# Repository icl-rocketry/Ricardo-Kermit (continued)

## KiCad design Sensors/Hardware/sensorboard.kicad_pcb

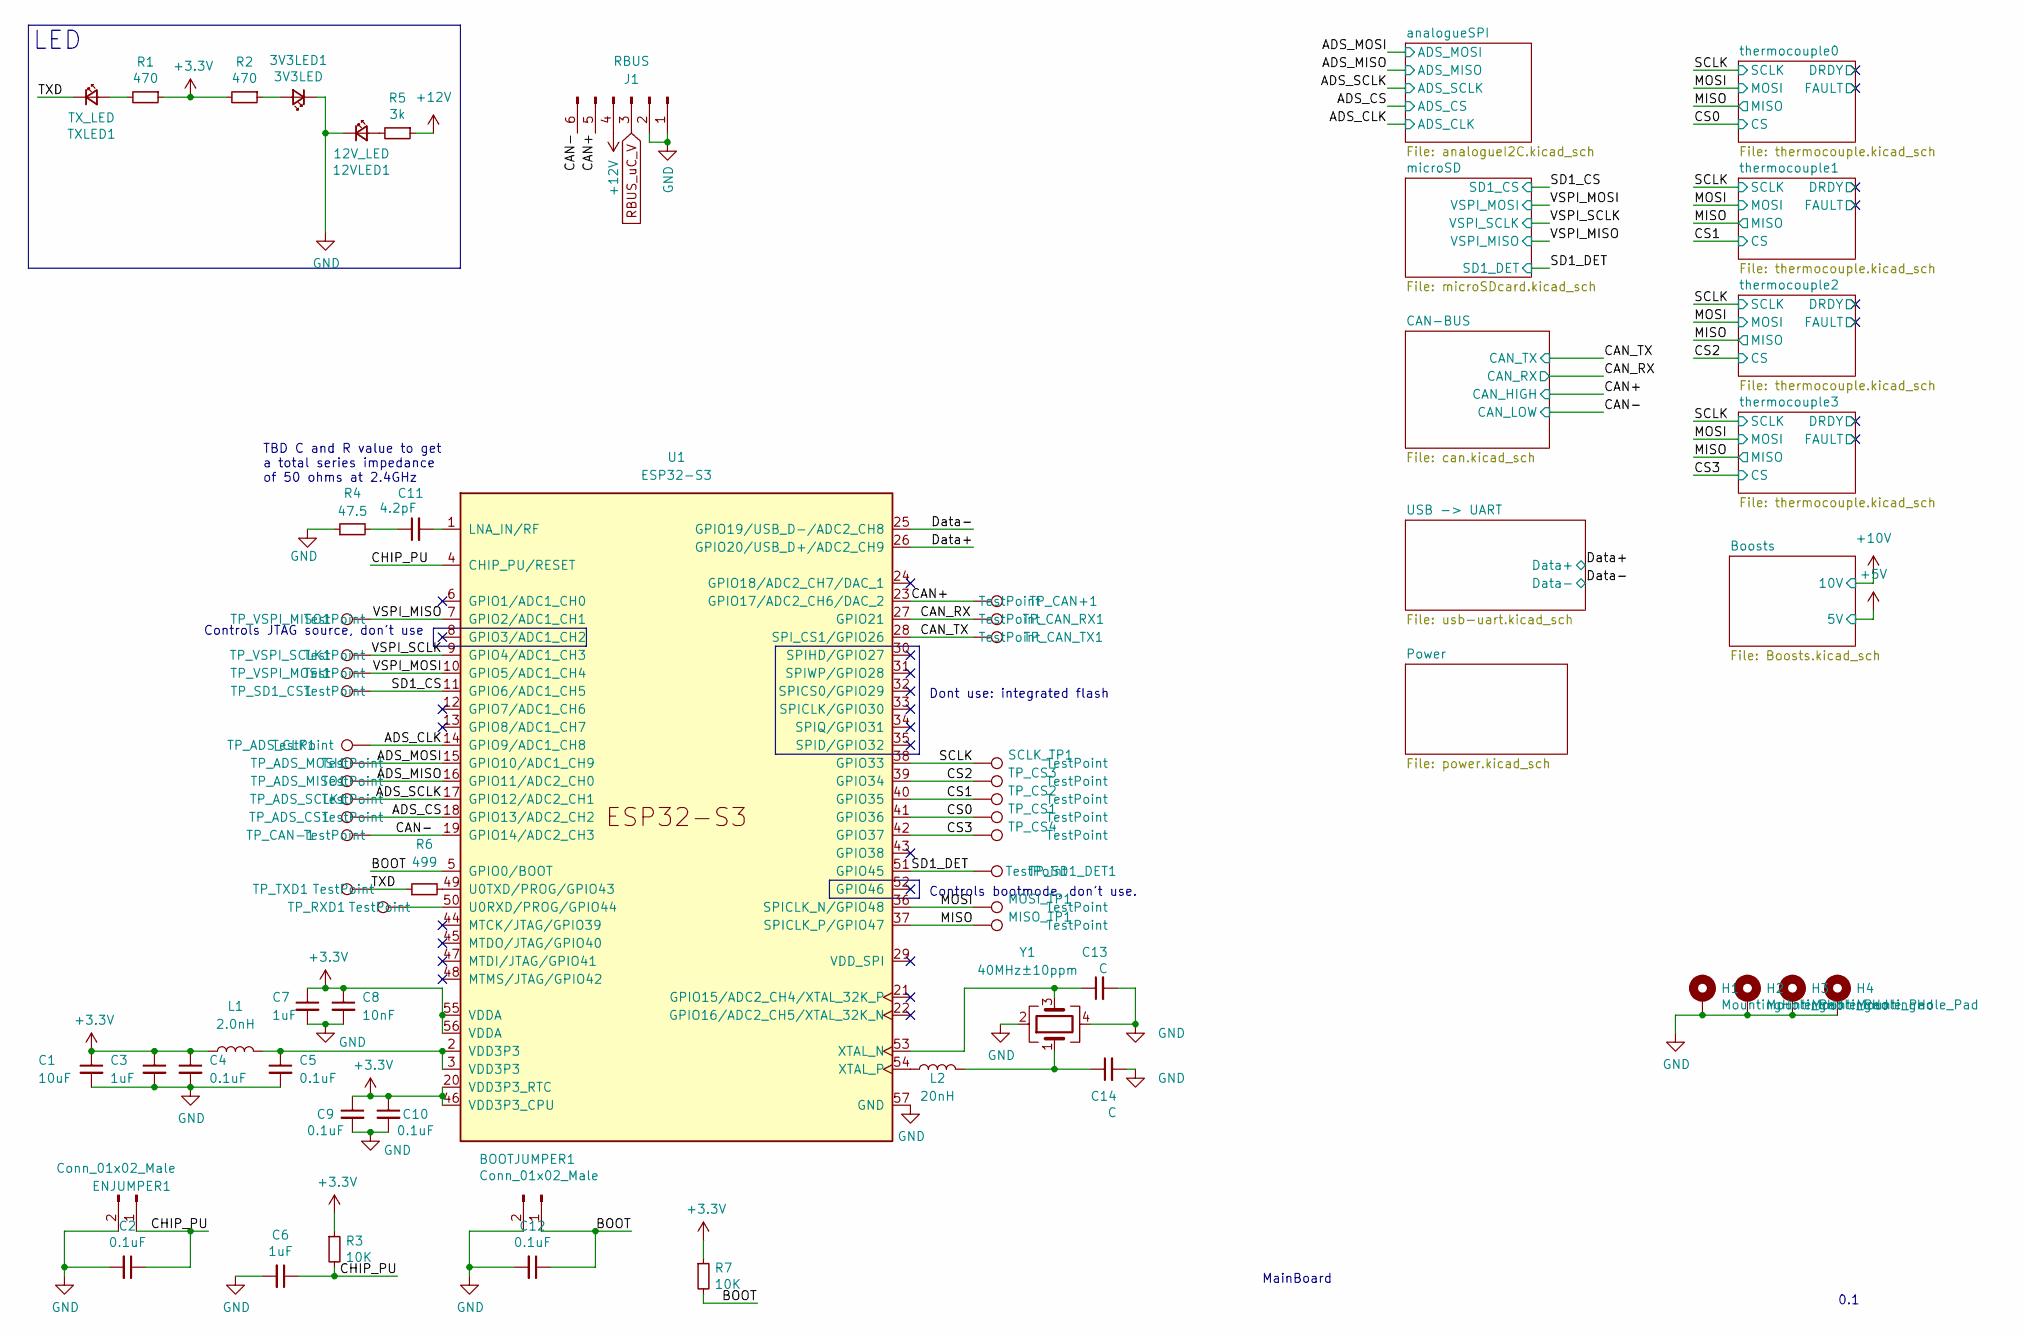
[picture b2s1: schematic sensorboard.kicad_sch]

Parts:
3V3LED1: 3V3LED; LED_0603_1608Metric
12VLED1: 12V_LED; LED_0603_1608Metric
BOOTJUMPER1: Conn_01x02_Male; PinHeader_1x02_P2.54mm_Vertical
C1: 10uF; C_0402_1005Metric
C2, C4, C5, C9, C10, C12: 0.1uF; C_0402_1005Metric
C3, C6, C7: 1uF; C_0402_1005Metric
C8: 10nF; C_0402_1005Metric
C11: 4.2pF; C_0402_1005Metric
C13, C14: C; C_0603_1608Metric
ENJUMPER1: Conn_01x02_Male; PinHeader_1x02_P2.54mm_Vertical
H1, H2, H3, H4: MountingHole_Pad; MountingHole_3.2mm_M3_DIN965_Pad
J1: RBUS; Molex_Mini-Fit_Jr_5566-06A_2x03_P4.20mm_Vertical
L1: 2.0nH; L_0402_1005Metric
L2: 20nH; L_0402_1005Metric
MISO_TP1: TestPoint; TestPoint_Pad_D1.0mm
MOSI_TP1: TestPoint; TestPoint_Pad_D1.0mm
R1, R2: 470; R_0603_1608Metric
R3, R7: 10K; R_0402_1005Metric
R4: 47.5; R_0402_1005Metric
R5: 3k; R_0402_1005Metric
R6: 499; R_0402_1005Metric
SCLK_TP1: TestPoint; TestPoint_Pad_D1.0mm
TP_ADS_CLK1: TestPoint; TestPoint_Pad_D1.0mm
TP_ADS_CS1: TestPoint; TestPoint_Pad_D1.0mm
TP_ADS_MISO1: TestPoint; TestPoint_Pad_D1.0mm
TP_ADS_MOSI1: TestPoint; TestPoint_Pad_D1.0mm
TP_ADS_SCLK1: TestPoint; TestPoint_Pad_D1.0mm
TP_CAN+1: TestPoint; TestPoint_Pad_D1.0mm
TP_CAN-1: TestPoint; TestPoint_Pad_D1.0mm
TP_CAN_RX1: TestPoint; TestPoint_Pad_D1.0mm
TP_CAN_TX1: TestPoint; TestPoint_Pad_D1.0mm
TP_CS1, TP_CS2, TP_CS3, TP_CS4: TestPoint; TestPoint_Pad_D1.0mm
TP_RXD1: TestPoint; TestPoint_Pad_D1.0mm
TP_SD1_CS1, TP_SD1_DET1: TestPoint; TestPoint_Pad_D1.0mm
TP_TXD1: TestPoint; TestPoint_Pad_D1.0mm
TP_VSPI_MISO1: TestPoint; TestPoint_Pad_D1.0mm
TP_VSPI_MOSI1: TestPoint; TestPoint_Pad_D1.0mm
TP_VSPI_SCLK1: TestPoint; TestPoint_Pad_D1.0mm
TXLED1: TX_LED; LED_0603_1608Metric
U1: ESP32-S3; QFN-56-1EP_7x7mm_P0.4mm_EP5.6x5.6mm
Y1: 40MHz±10ppm; Crystal_SMD_2016-4Pin_2.0x1.6mm

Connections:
+3V3: C1.1, C3.1, C4.1, C7.1, C8.1, C9.1, C10.1, L1.1, R1.1, R2.2, R3.1, R7.1, U1.20 (VDD3P3_RTC), U1.46 (VDD3P3_CPU), U1.55 (VDDA), U1.56 (VDDA); also elsewhere on the board
+12V: J1.4, R5.1
/ADS_CLK: TP_ADS_CLK1.1, U1.14 (GPIO9/ADC1_CH8); also elsewhere on the board
/ADS_CS: TP_ADS_CS1.1, U1.18 (GPIO13/ADC2_CH2); also elsewhere on the board
/ADS_MISO: TP_ADS_MISO1.1, U1.16 (GPIO11/ADC2_CH0); also elsewhere on the board
/ADS_MOSI: TP_ADS_MOSI1.1, U1.15 (GPIO10/ADC1_CH9); also elsewhere on the board
/ADS_SCLK: TP_ADS_SCLK1.1, U1.17 (GPIO12/ADC2_CH1); also elsewhere on the board
/BOOT: BOOTJUMPER1.1, C12.1, R7.2, U1.5 (GPIO0/BOOT)
/CAN+: J1.5, TP_CAN+1.1, U1.23 (GPIO17/ADC2_CH6/DAC_2); also elsewhere on the board
/CAN-: J1.6, TP_CAN-1.1, U1.19 (GPIO14/ADC2_CH3); also elsewhere on the board
/CAN_RX: TP_CAN_RX1.1, U1.27 (GPIO21); also elsewhere on the board
/CAN_TX: TP_CAN_TX1.1, U1.28 (SPI_CS1/GPIO26); also elsewhere on the board
/CHIP_PU: C2.1, C6.1, ENJUMPER1.1, R3.2, U1.4 (CHIP_PU/RESET)
/CS0: TP_CS1.1, U1.41 (GPIO36); also elsewhere on the board
/CS1: TP_CS2.1, U1.40 (GPIO35); also elsewhere on the board
/CS2: TP_CS3.1, U1.39 (GPIO34); also elsewhere on the board
/CS3: TP_CS4.1, U1.42 (GPIO37); also elsewhere on the board
/Data+: U1.26 (GPIO20/USB_D+/ADC2_CH9); also elsewhere on the board
/Data-: U1.25 (GPIO19/USB_D-/ADC2_CH8); also elsewhere on the board
/MISO: MISO_TP1.1, U1.37 (SPICLK_P/GPIO47); also elsewhere on the board
/MOSI: MOSI_TP1.1, U1.36 (SPICLK_N/GPIO48); also elsewhere on the board
/SCLK: SCLK_TP1.1, U1.38 (GPIO33); also elsewhere on the board
/SD1_CS: TP_SD1_CS1.1, U1.11 (GPIO6/ADC1_CH5); also elsewhere on the board
/SD1_DET: TP_SD1_DET1.1, U1.51 (GPIO45); also elsewhere on the board
/TXD: R6.1, TP_TXD1.1, TXLED1.1 (K)
/VSPI_MISO: TP_VSPI_MISO1.1, U1.7 (GPIO2/ADC1_CH1); also elsewhere on the board
/VSPI_MOSI: TP_VSPI_MOSI1.1, U1.10 (GPIO5/ADC1_CH4); also elsewhere on the board
/VSPI_SCLK: TP_VSPI_SCLK1.1, U1.9 (GPIO4/ADC1_CH3); also elsewhere on the board
GND: 3V3LED1.1 (K), 12VLED1.1 (K), BOOTJUMPER1.2, C1.2, C2.2, C3.2, C4.2, C5.2, C6.2, C7.2, C8.2, C9.2, C10.2, C12.2, C13.2, C14.2, ENJUMPER1.2, H1.1, H2.1, H3.1, H4.1, J1.1, J1.2, R4.1, U1.57 (GND), Y1.2, Y1.4; also elsewhere on the board
unnamed: 3V3LED1.2 (A), R2.1
unnamed: 12VLED1.2 (A), R5.2
unnamed: C5.1, L1.2, U1.2 (VDD3P3), U1.3 (VDD3P3)
unnamed: C11.1, R4.2
unnamed: C14.1, L2.2, Y1.1
unnamed: R1.2, TXLED1.2 (A)
unnamed: C11.2, U1.1 (LNA_IN/RF)
unnamed: TP_RXD1.1, U1.50 (U0RXD/PROG/GPIO44)
unnamed: R6.2, U1.49 (U0TXD/PROG/GPIO43)
unnamed: C13.1, U1.53 (XTAL_N), Y1.3
unnamed: L2.1, U1.54 (XTAL_P)
RBUS_uC_V: J1.3; also elsewhere on the board

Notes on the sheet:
LED
Dont use: integrated flash
TBD C and R value to get a total series impedance of 50 ohms at 2.4GHz
MainBoard
0.1
Controls JTAG source, don't use
Controls bootmode, don't use.

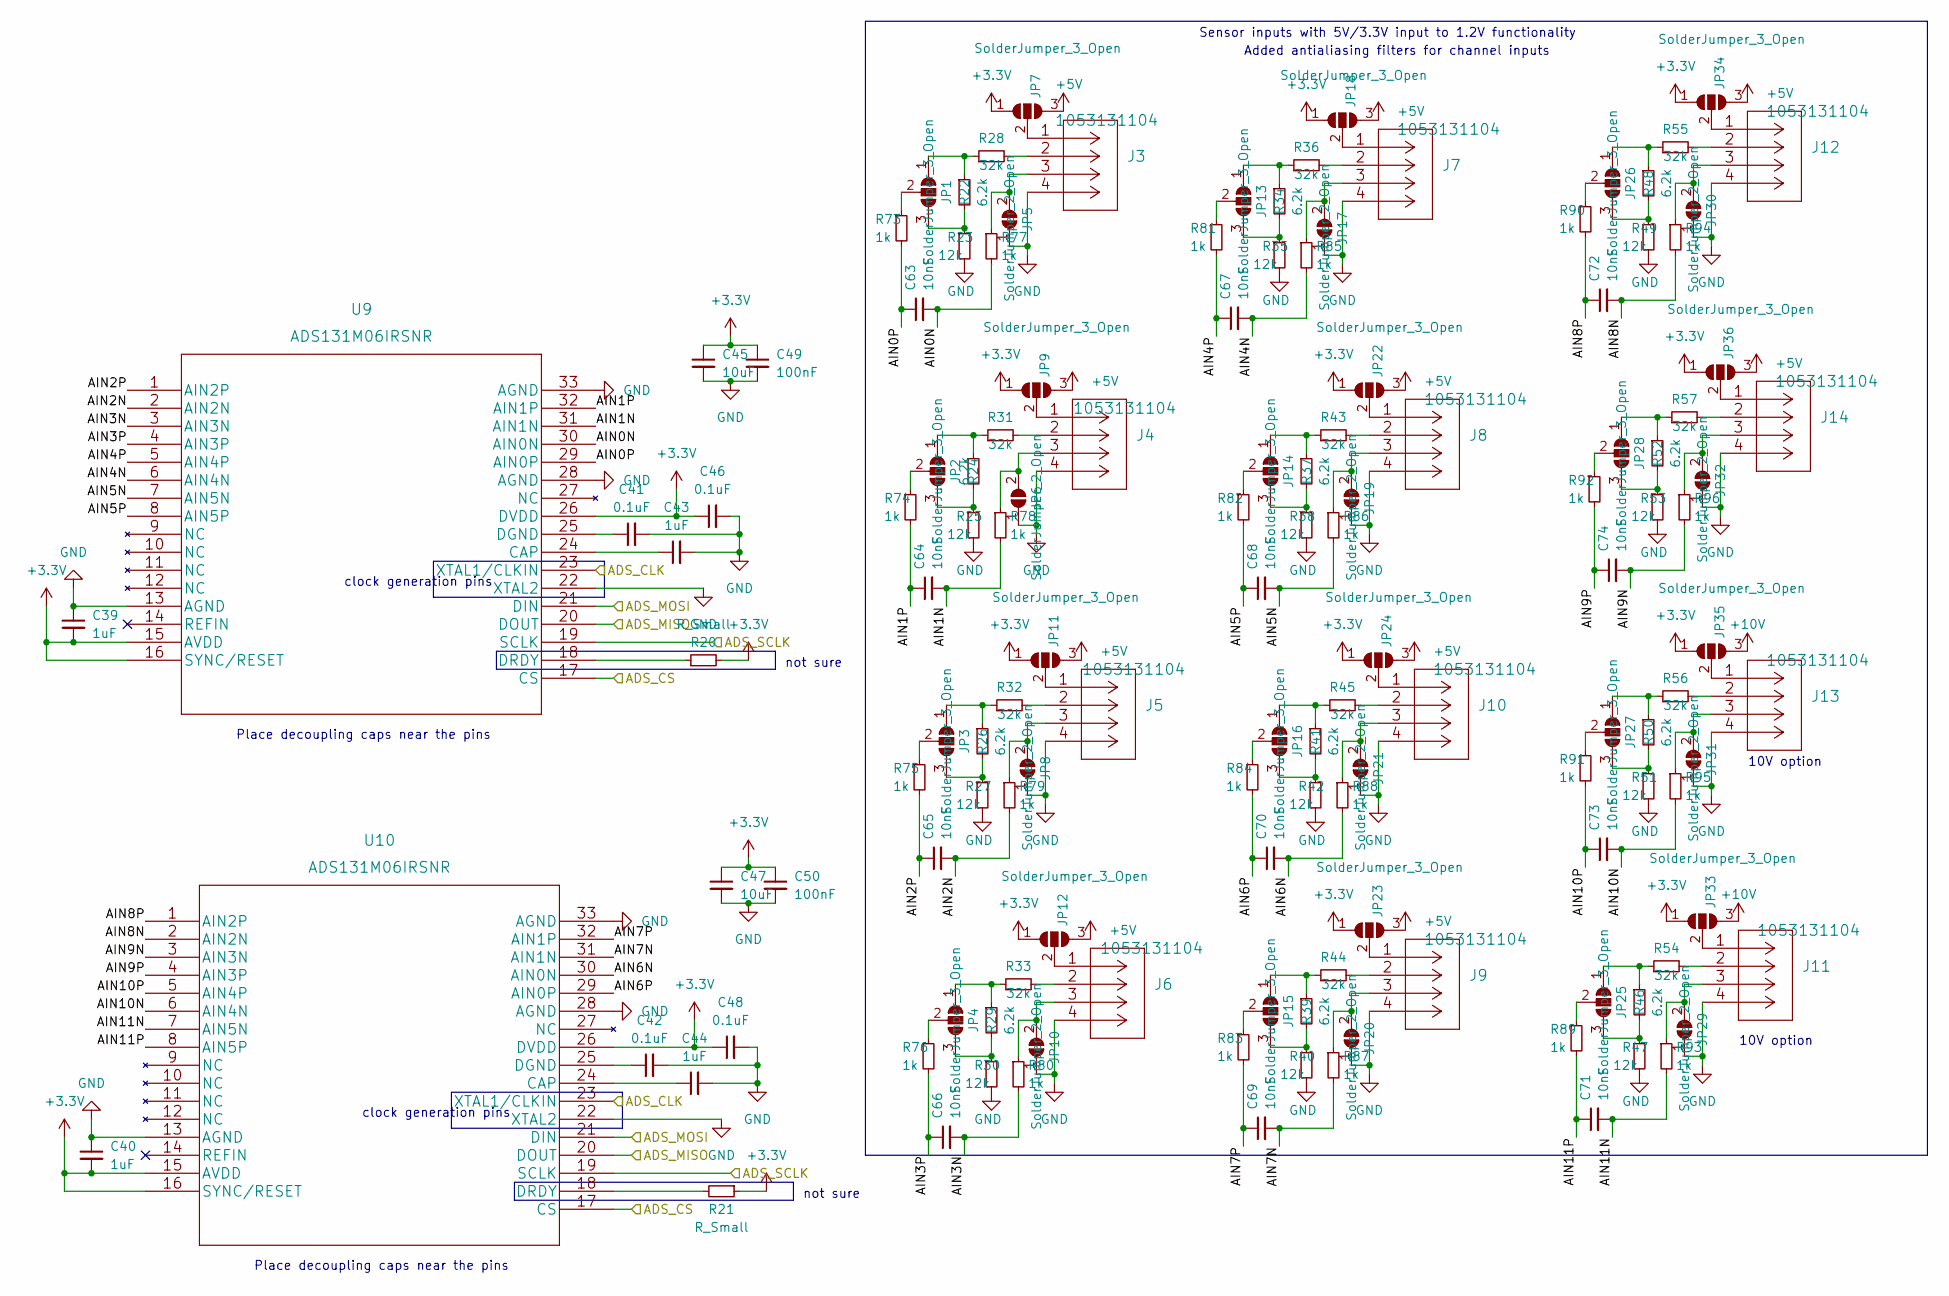
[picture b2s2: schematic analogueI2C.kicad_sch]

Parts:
C39, C40, C43, C44: 1uF; C_0402_1005Metric
C41, C42, C46, C48: 0.1uF; C_0402_1005Metric
C45, C47: 10uF; C_0402_1005Metric
C49, C50: 100nF; C_0402_1005Metric
C63, C64, C65, C66, C67, C68, C69, C70, C71, C72, C73, C74: 10nF; C_0402_1005Metric
J3, J4, J5, J6, J7, J8, J9, J10, J11, J12, J13, J14: 1053131104
JP1, JP2, JP3, JP4, JP7, JP9, JP11, JP12, JP13, JP14, JP15, JP16, JP18, JP22, JP23, JP24, JP25, JP26, JP27, JP28, JP33, JP34, JP35, JP36: SolderJumper_3_Open; SolderJumper-3_P1.3mm_Open_RoundedPad1.0x1.5mm_NumberLabels
JP5, JP6, JP8, JP10, JP17, JP19, JP20, JP21, JP29, JP30, JP31, JP32: SolderJumper_2_Open; SolderJumper-2_P1.3mm_Open_RoundedPad1.0x1.5mm
R20, R21: R_Small; R_0603_1608Metric
R22, R24, R26, R29, R34, R37, R39, R41, R46, R48, R50, R52: 6.2k; R_0402_1005Metric
R23, R25, R27, R30, R35, R38, R40, R42, R47, R49, R51, R53: 12k; R_0402_1005Metric
R28, R31, R32, R33, R36, R43, R44, R45, R54, R55, R56, R57: 32k; R_0402_1005Metric
R73, R74, R75, R76, R77, R78, R79, R80, R81, R82, R83, R84, R85, R86, R87, R88, R89, R90, R91, R92, R93, R94, R95, R96: 1k; R_0402_1005Metric
U9, U10: ADS131M06IRSNR

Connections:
+3V3: C39.2, C40.2, C45.1, C46.1, C47.1, C48.1, C49.1, C50.1, JP7.1 (A), JP9.1 (A), JP11.1 (A), JP12.1 (A), JP18.1 (A), JP22.1 (A), JP23.1 (A), JP24.1 (A), JP33.1 (A), JP34.1 (A), JP35.1 (A), JP36.1 (A), R20.2, R21.1, U9.15 (AVDD), U9.16 (SYNC/RESET), U9.26 (DVDD), U10.15 (AVDD), U10.16 (SYNC/RESET), U10.26 (DVDD); also elsewhere on the board
+5V: JP7.3 (B), JP9.3 (B), JP11.3 (B), JP12.3 (B), JP18.3 (B), JP22.3 (B), JP23.3 (B), JP24.3 (B), JP34.3 (B), JP36.3 (B); also elsewhere on the board
+10V: JP33.3 (B), JP35.3 (B); also elsewhere on the board
/ADS_CLK: U9.23 (XTAL1/CLKIN), U10.23 (XTAL1/CLKIN); also elsewhere on the board
/ADS_CS: U9.17 (CS), U10.17 (CS); also elsewhere on the board
/ADS_MISO: U9.20 (DOUT), U10.20 (DOUT); also elsewhere on the board
/ADS_MOSI: U9.21 (DIN), U10.21 (DIN); also elsewhere on the board
/ADS_SCLK: U9.19 (SCLK), U10.19 (SCLK); also elsewhere on the board
/analogueSPI/AIN0N: C63.2, R77.2, U9.30 (AIN0N)
/analogueSPI/AIN0P: C63.1, R73.2, U9.29 (AIN0P)
/analogueSPI/AIN1N: C64.2, R78.2, U9.31 (AIN1N)
/analogueSPI/AIN1P: C64.1, R74.2, U9.32 (AIN1P)
/analogueSPI/AIN2N: C65.2, R79.2, U9.2 (AIN2N)
/analogueSPI/AIN2P: C65.1, R75.2, U9.1 (AIN2P)
/analogueSPI/AIN3N: C66.2, R80.2, U9.3 (AIN3N)
/analogueSPI/AIN3P: C66.1, R76.2, U9.4 (AIN3P)
/analogueSPI/AIN4N: C67.2, R85.2, U9.6 (AIN4N)
/analogueSPI/AIN4P: C67.1, R81.2, U9.5 (AIN4P)
/analogueSPI/AIN5N: C68.2, R86.2, U9.7 (AIN5N)
/analogueSPI/AIN5P: C68.1, R82.2, U9.8 (AIN5P)
/analogueSPI/AIN6N: C70.2, R88.2, U10.30 (AIN0N)
/analogueSPI/AIN6P: C70.1, R84.2, U10.29 (AIN0P)
/analogueSPI/AIN7N: C69.2, R87.2, U10.31 (AIN1N)
/analogueSPI/AIN7P: C69.1, R83.2, U10.32 (AIN1P)
/analogueSPI/AIN8N: C72.2, R94.2, U10.2 (AIN2N)
/analogueSPI/AIN8P: C72.1, R90.2, U10.1 (AIN2P)
/analogueSPI/AIN9N: C74.2, R96.2, U10.3 (AIN3N)
/analogueSPI/AIN9P: C74.1, R92.2, U10.4 (AIN3P)
/analogueSPI/AIN10N: C73.2, R95.2, U10.6 (AIN4N)
/analogueSPI/AIN10P: C73.1, R91.2, U10.5 (AIN4P)
/analogueSPI/AIN11N: C71.2, R93.2, U10.7 (AIN5N)
/analogueSPI/AIN11P: C71.1, R89.2, U10.8 (AIN5P)
GND: C39.1, C40.1, C41.2, C42.2, C43.2, C44.2, C45.2, C46.2, C47.2, C48.2, C49.2, C50.2, J3.4, J4.4, J5.4, J6.4, J7.4, J8.4, J9.4, J10.4, J11.4, J12.4, J13.4, J14.4, JP5.1 (A), JP6.1 (A), JP8.1 (A), JP10.1 (A), JP17.1 (A), JP19.1 (A), JP20.1 (A), JP21.1 (A), JP29.1 (A), JP30.1 (A), JP31.1 (A), JP32.1 (A), R23.2, R25.2, R27.2, R30.2, R35.2, R38.2, R40.2, R42.2, R47.2, R49.2, R51.2, R53.2, U9.13 (AGND), U9.22 (XTAL2), U9.28 (AGND), U9.33 (AGND), U10.13 (AGND), U10.22 (XTAL2), U10.28 (AGND), U10.33 (AGND); also elsewhere on the board
unnamed: J3.2, R28.2
unnamed: J4.2, R31.2
unnamed: J5.2, R32.2
unnamed: J6.2, R33.2
unnamed: J7.2, R36.2
unnamed: J8.2, R43.2
unnamed: J9.2, R44.2
unnamed: J10.2, R45.2
unnamed: J11.2, R54.2
unnamed: J12.2, R55.2
unnamed: J13.2, R56.2
unnamed: J14.2, R57.2
unnamed: JP1.1 (A), R22.1, R28.1
unnamed: JP1.3 (B), R22.2, R23.1
unnamed: JP1.2 (C), R73.1
unnamed: JP2.1 (A), R24.1, R31.1
unnamed: JP2.3 (B), R24.2, R25.1
unnamed: JP2.2 (C), R74.1
unnamed: JP3.1 (A), R26.1, R32.1
unnamed: JP3.3 (B), R26.2, R27.1
unnamed: JP3.2 (C), R75.1
unnamed: JP4.1 (A), R29.1, R33.1
unnamed: JP4.3 (B), R29.2, R30.1
unnamed: JP4.2 (C), R76.1
unnamed: J3.3, JP5.2 (B), R77.1
unnamed: J4.3, JP6.2 (B), R78.1
unnamed: J3.1, JP7.2 (C)
unnamed: J5.3, JP8.2 (B), R79.1
unnamed: J4.1, JP9.2 (C)
unnamed: J6.3, JP10.2 (B), R80.1
unnamed: J5.1, JP11.2 (C)
unnamed: J6.1, JP12.2 (C)
unnamed: JP13.1 (A), R34.1, R36.1
unnamed: JP13.3 (B), R34.2, R35.1
unnamed: JP13.2 (C), R81.1
unnamed: JP14.1 (A), R37.1, R43.1
unnamed: JP14.3 (B), R37.2, R38.1
unnamed: JP14.2 (C), R82.1
unnamed: JP15.1 (A), R39.1, R44.1
unnamed: JP15.3 (B), R39.2, R40.1
unnamed: JP15.2 (C), R83.1
unnamed: JP16.1 (A), R41.1, R45.1
unnamed: JP16.3 (B), R41.2, R42.1
unnamed: JP16.2 (C), R84.1
unnamed: J7.3, JP17.2 (B), R85.1
unnamed: J7.1, JP18.2 (C)
unnamed: J8.3, JP19.2 (B), R86.1
unnamed: J9.3, JP20.2 (B), R87.1
unnamed: J10.3, JP21.2 (B), R88.1
unnamed: J8.1, JP22.2 (C)
unnamed: J9.1, JP23.2 (C)
unnamed: J10.1, JP24.2 (C)
unnamed: JP25.1 (A), R46.1, R54.1
unnamed: JP25.3 (B), R46.2, R47.1
unnamed: JP25.2 (C), R89.1
unnamed: JP26.1 (A), R48.1, R55.1
unnamed: JP26.3 (B), R48.2, R49.1
unnamed: JP26.2 (C), R90.1
unnamed: JP27.1 (A), R50.1, R56.1
unnamed: JP27.3 (B), R50.2, R51.1
unnamed: JP27.2 (C), R91.1
unnamed: JP28.1 (A), R52.1, R57.1
unnamed: JP28.3 (B), R52.2, R53.1
unnamed: JP28.2 (C), R92.1
unnamed: J11.3, JP29.2 (B), R93.1
unnamed: J12.3, JP30.2 (B), R94.1
unnamed: J13.3, JP31.2 (B), R95.1
unnamed: J14.3, JP32.2 (B), R96.1
unnamed: J11.1, JP33.2 (C)
unnamed: J12.1, JP34.2 (C)
unnamed: J13.1, JP35.2 (C)
unnamed: J14.1, JP36.2 (C)
unnamed: C43.1, U9.24 (CAP)
unnamed: C41.1, U9.25 (DGND)
unnamed: R20.1, U9.18 (DRDY)
unnamed: C44.1, U10.24 (CAP)
unnamed: C42.1, U10.25 (DGND)
unnamed: R21.2, U10.18 (DRDY)

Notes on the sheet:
Added antialiasing filters for channel inputs
10V option
clock generation pins
not sure
Sensor inputs with 5V/3.3V input to 1.2V functionality
Place decoupling caps near the pins

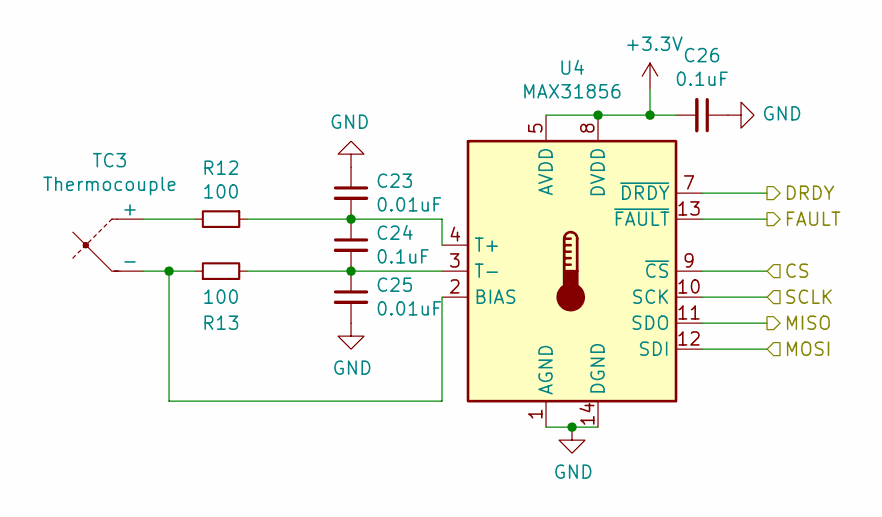
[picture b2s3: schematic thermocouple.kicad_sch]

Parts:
C23, C25: 0.01uF; C_0402_1005Metric
C24, C26: 0.1uF; C_0402_1005Metric
R12, R13: 100; R_0402_1005Metric
TC3: Thermocouple; TerminalBlock_TE_282834-2_1x02_P2.54mm_Horizontal
U4: MAX31856; TSSOP-14_4.4x5mm_P0.65mm

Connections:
+3V3: C26.2, U4.5 (AVDD), U4.8 (DVDD); also elsewhere on the board
/CS3: U4.9 (~CS); also elsewhere on the board
/MISO: U4.11 (SDO); also elsewhere on the board
/MOSI: U4.12 (SDI); also elsewhere on the board
/SCLK: U4.10 (SCK); also elsewhere on the board
/thermocouple3/DRDY: U4.7 (~DRDY)
/thermocouple3/FAULT: U4.13 (~FAULT)
GND: C23.1, C25.2, C26.1, U4.1 (AGND), U4.14 (DGND); also elsewhere on the board
unnamed: R12.2, TC3.1 (+)
unnamed: R13.1, TC3.2 (-), U4.2 (BIAS)
unnamed: C23.2, C24.1, R12.1, U4.4 (T+)
unnamed: C24.2, C25.1, R13.2, U4.3 (T-)

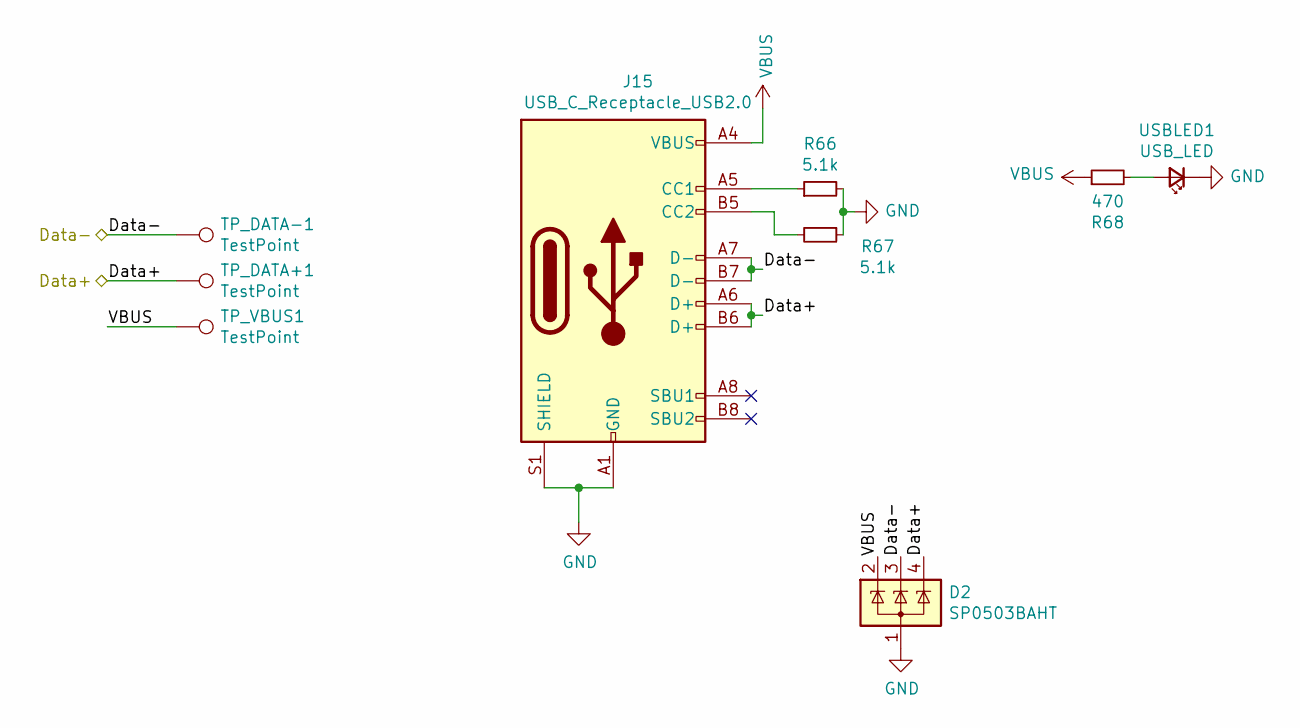
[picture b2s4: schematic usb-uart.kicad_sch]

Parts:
D2: SP0503BAHT; SOT-143
J15: USB_C_Receptacle_USB2.0; USB_C_Receptacle_Palconn_UTC16-G
R66, R67: 5.1k; R_0402_1005Metric
R68: 470; R_0402_1005Metric
TP_DATA+1: TestPoint; TestPoint_Pad_D1.0mm
TP_DATA-1: TestPoint; TestPoint_Pad_D1.0mm
TP_VBUS1: TestPoint; TestPoint_Pad_D1.0mm
USBLED1: USB_LED; LED_0603_1608Metric

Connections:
/Data+: D2.4 (K), J15.A6 (D+), J15.B6 (D+), TP_DATA+1.1; also elsewhere on the board
/Data-: D2.3 (K), J15.A7 (D-), J15.B7 (D-), TP_DATA-1.1; also elsewhere on the board
GND: D2.1 (A), J15.A1 (GND), J15.A12 (GND), J15.B1 (GND), J15.B12 (GND), J15.S1 (SHIELD), R66.2, R67.1, USBLED1.1 (K); also elsewhere on the board
unnamed: J15.A5 (CC1), R66.1
unnamed: J15.B5 (CC2), R67.2
unnamed: R68.2, USBLED1.2 (A)
VBUS: D2.2 (K), J15.A4 (VBUS), J15.A9 (VBUS), J15.B4 (VBUS), J15.B9 (VBUS), R68.1, TP_VBUS1.1; also elsewhere on the board

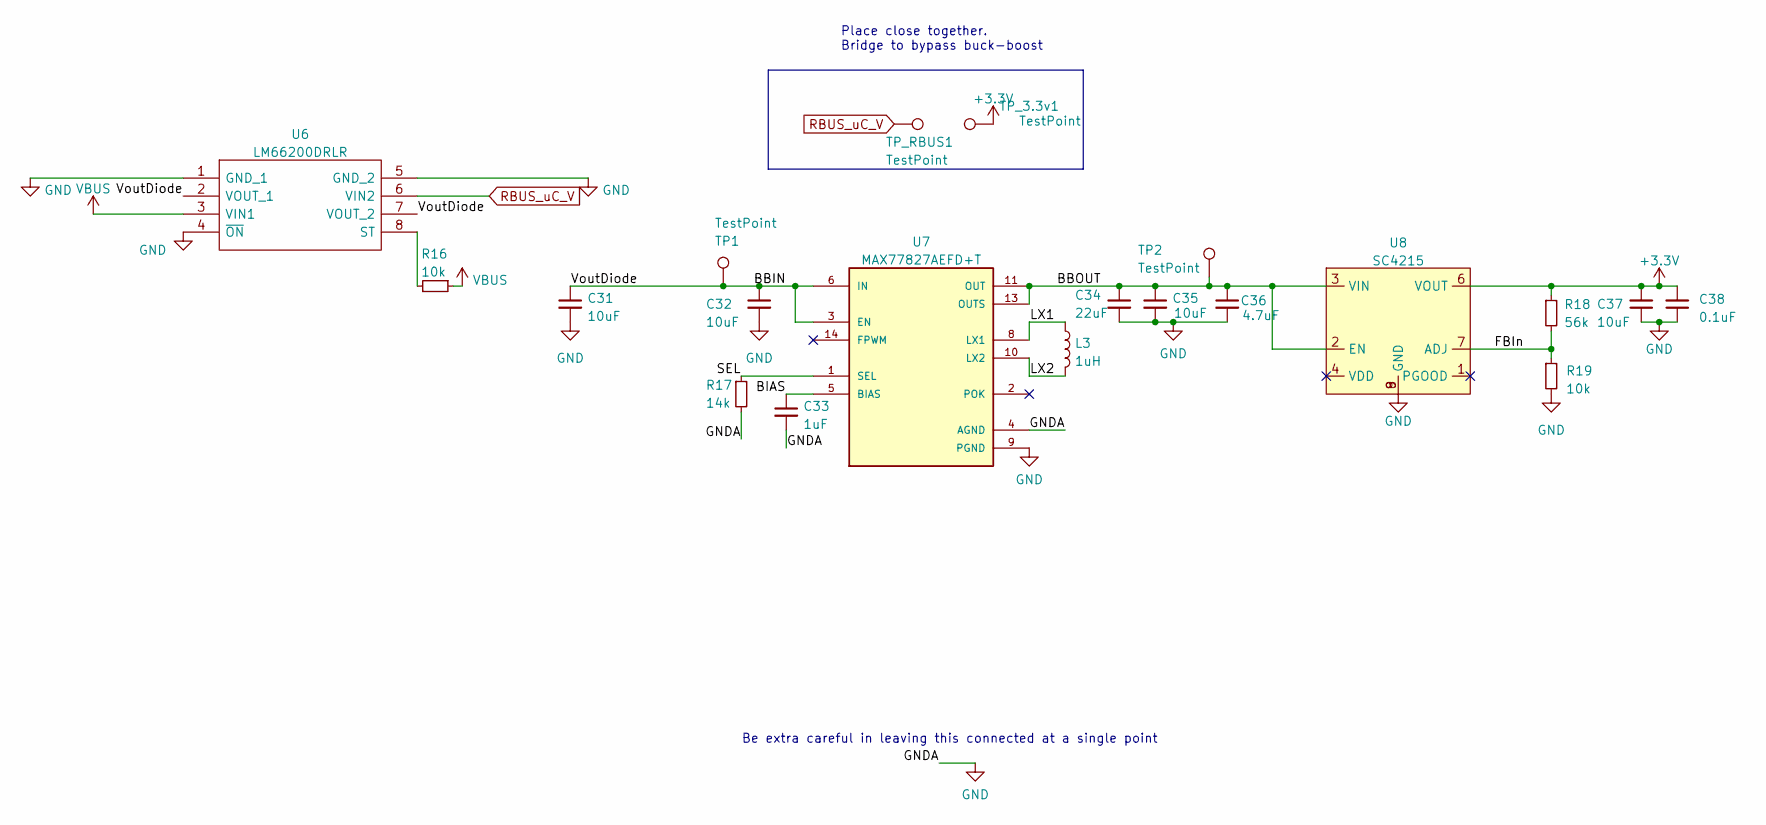
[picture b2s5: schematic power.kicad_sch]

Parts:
C31, C35, C37: 10uF; C_0402_1005Metric
C32: 10uF; C_0603_1608Metric
C33: 1uF; C_0402_1005Metric
C34: 22uF; C_0603_1608Metric
C36: 4.7uF; C_0402_1005Metric
C38: 0.1uF; C_0402_1005Metric
L3: 1uH; L_0805_2012Metric
R16, R19: 10k; R_0402_1005Metric
R17: 14k; R_0402_1005Metric
R18: 56k; R_0402_1005Metric
TP1, TP2: TestPoint; TestPoint_Pad_D1.0mm
TP_3.3v1: TestPoint; TestPoint_Pad_D1.0mm
TP_RBUS1: TestPoint; TestPoint_Pad_D1.0mm
U6: LM66200DRLR; SOTFL50P160X60-8N; Manufacturer_Part_Number LM66200DRLR; Mouser Part Number 595-LM66200DRLR
U7: MAX77827AEFD+T; CONV_MAX77827AEFD+T; PARTREV B
U8: SC4215; SOIC127P599X175-9N

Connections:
+3V3: C37.2, C38.2, R18.1, TP_3.3v1.1, U8.6 (VOUT); also elsewhere on the board
/Power/BBIN: C31.1, C32.1, TP1.1, U6.2 (VOUT_1), U6.7 (VOUT_2), U7.3 (EN), U7.6 (IN)
/Power/BBOUT: C34.1, C35.1, C36.1, TP2.1, U7.11 (OUT), U7.13 (OUTS), U8.2 (EN), U8.3 (VIN)
/Power/BIAS: C33.1, U7.5 (BIAS)
/Power/FBIn: R18.2, R19.1, U8.7 (ADJ)
/Power/LX1: L3.1, U7.8 (LX1)
/Power/LX2: L3.2, U7.10 (LX2)
/Power/SEL: R17.1, U7.1 (SEL)
GND: C31.2, C32.2, C33.2, C34.2, C35.2, C36.2, C37.1, C38.1, R17.2, R19.2, U6.1 (GND_1), U6.4 (~ON), U6.5 (GND_2), U7.4 (AGND), U7.9 (PGND), U8.8 (GND), U8.9 (GND); also elsewhere on the board
unnamed: R16.2, U6.8 (ST)
RBUS_uC_V: TP_RBUS1.1, U6.6 (VIN2); also elsewhere on the board
VBUS: R16.1, U6.3 (VIN1); also elsewhere on the board

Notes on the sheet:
Place close together. Bridge to bypass buck-boost
Be extra careful in leaving this connected at a single point

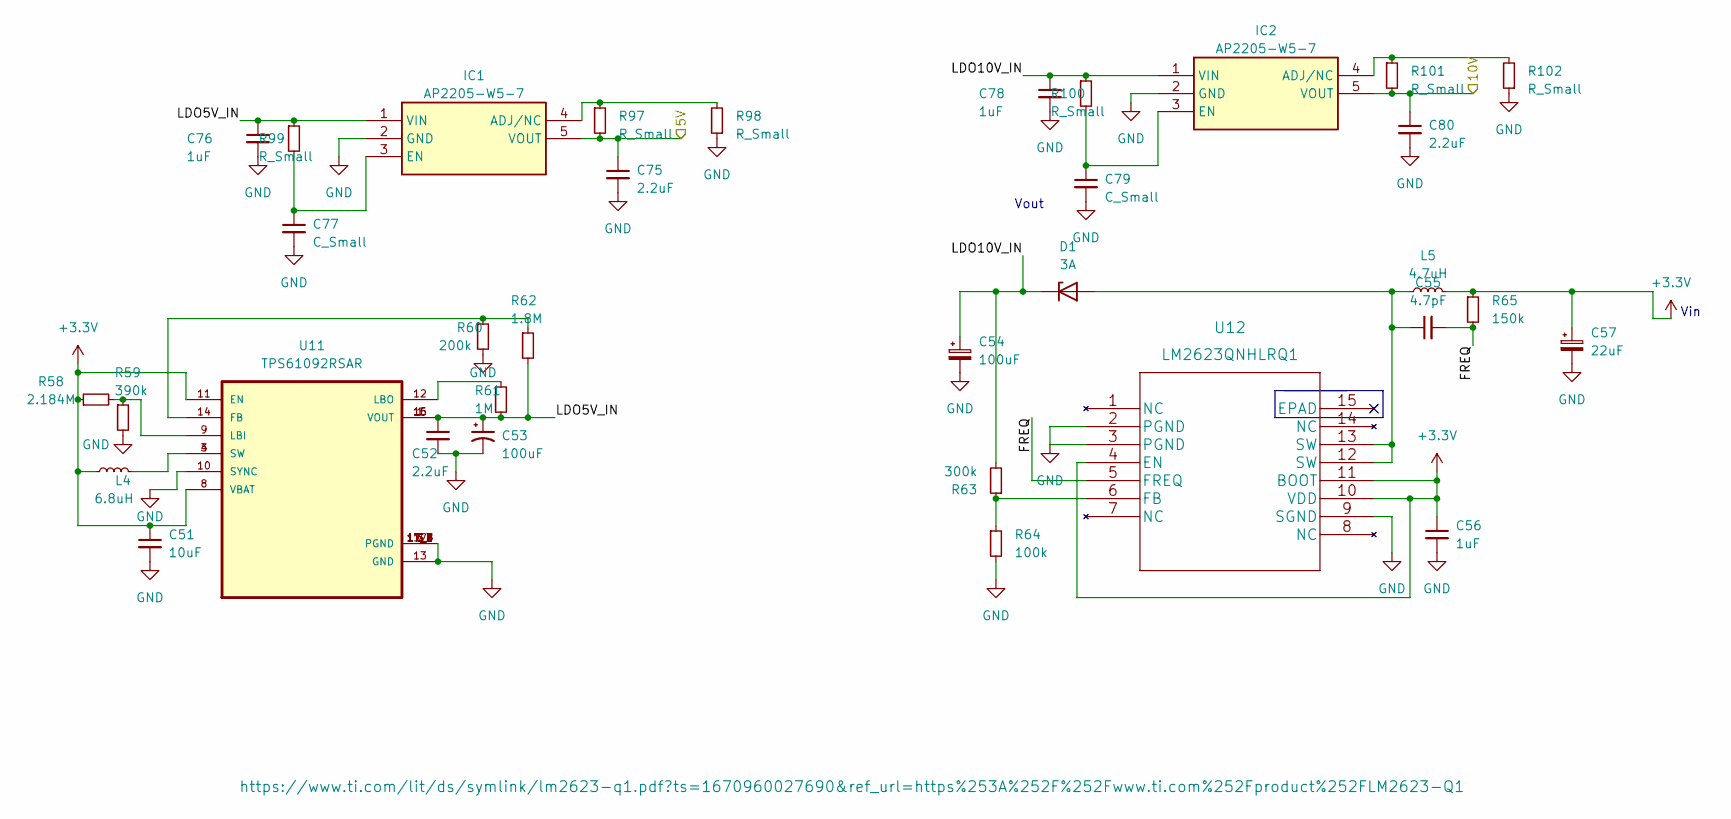
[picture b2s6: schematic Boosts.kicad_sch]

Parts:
C51: 10uF; C_0603_1608Metric
C52: 2.2uF; C_0603_1608Metric
C53: 100uF; CAPC2012X145N
C54: 100uF; C_0603_1608Metric
C55: 4.7pF; C_0402_1005Metric
C56, C76, C78: 1uF; C_0402_1005Metric
C57: 22uF; C_0603_1608Metric
C75, C80: 2.2uF; C_0402_1005Metric
C77, C79: C_Small; C_0402_1005Metric
D1: 3A; D_0603_1608Metric
IC1, IC2: AP2205-W5-7; SOT95P282X145-5N; Mouser Part Number 621-AP2205-W5-7
L4: 6.8uH; INDPM3030X200N
L5: 4.7uH; L_0603_1608Metric
R58: 2.184M; R_0603_1608Metric
R59: 390k; R_0603_1608Metric
R60: 200k; R_0603_1608Metric
R61: 1M; R_0603_1608Metric
R62: 1.8M; R_0603_1608Metric
R63: 300k; R_0402_1005Metric
R64: 100k; R_0402_1005Metric
R65: 150k; R_0402_1005Metric
R97, R98, R99, R100, R101, R102: R_Small; R_0402_1005Metric
U11: TPS61092RSAR; QFN65P400X400X100-17N
U12: LM2623QNHLRQ1

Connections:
+3V3: C51.1, C56.1, C57.1, L4.1, L5.2, R58.1, R65.1, U11.8 (VBAT), U11.11 (EN), U12.4 (EN), U12.10 (VDD), U12.11 (BOOT); also elsewhere on the board
+5V: C75.1, IC1.5 (VOUT), R97.2; also elsewhere on the board
+10V: C80.1, IC2.5 (VOUT), R101.2; also elsewhere on the board
/Boosts/FREQ: C55.2, R65.2, U12.5 (FREQ)
/Boosts/LDO5V_IN: C52.1, C53.1, C76.1, IC1.1 (VIN), R61.2, R62.2, R99.1, U11.1 (VOUT), U11.15 (VOUT), U11.16 (VOUT)
/Boosts/LDO10V_IN: C54.1, C78.1, D1.1 (K), IC2.1 (VIN), R63.2, R100.1
GND: C51.2, C52.2, C53.2, C54.2, C56.2, C57.2, C75.2, C76.2, C77.2, C78.2, C79.2, C80.2, IC1.2 (GND), IC2.2 (GND), R59.2, R60.2, R64.2, R98.1, R102.1, U11.5 (PGND), U11.6 (PGND), U11.7 (PGND), U11.10 (SYNC), U11.13 (GND), U11.17 (PGND), U11.17_1 (PGND), U11.17_2 (PGND), U11.17_3 (PGND), U11.17_4 (PGND), U11.17_5 (PGND), U11.17_6 (PGND), U11.17_7 (PGND), U11.17_8 (PGND), U11.17_9 (PGND), U12.2 (PGND), U12.3 (PGND), U12.9 (SGND); also elsewhere on the board
unnamed: C55.1, D1.2 (A), L5.1, U12.12 (SW), U12.13 (SW)
unnamed: IC1.4 (ADJ/NC), R97.1, R98.2
unnamed: C77.1, IC1.3 (EN), R99.2
unnamed: IC2.4 (ADJ/NC), R101.1, R102.2
unnamed: C79.1, IC2.3 (EN), R100.2
unnamed: L4.2, U11.3 (SW), U11.4 (SW)
unnamed: R60.1, R62.1, U11.14 (FB)
unnamed: R58.2, R59.1, U11.9 (LBI)
unnamed: R61.1, U11.12 (LBO)
unnamed: R63.1, R64.1, U12.6 (FB)

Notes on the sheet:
Vout
Vin

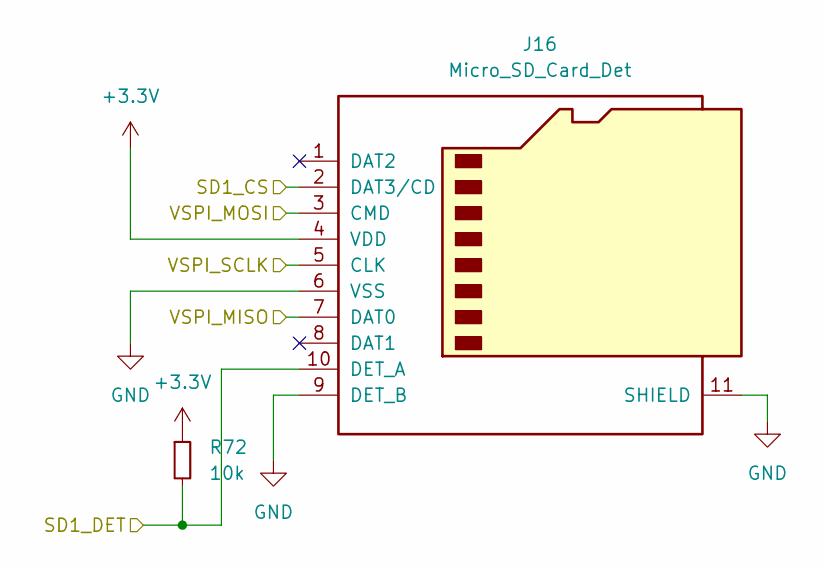
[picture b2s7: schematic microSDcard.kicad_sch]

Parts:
J16: Micro_SD_Card_Det; microSD_HC_Hirose_DM3AT-SF-PEJM5
R72: 10k; R_0402_1005Metric

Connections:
+3V3: J16.4 (VDD), R72.1; also elsewhere on the board
/SD1_CS: J16.2 (DAT3/CD); also elsewhere on the board
/SD1_DET: J16.10 (DET_A), R72.2; also elsewhere on the board
/VSPI_MISO: J16.7 (DAT0); also elsewhere on the board
/VSPI_MOSI: J16.3 (CMD); also elsewhere on the board
/VSPI_SCLK: J16.5 (CLK); also elsewhere on the board
GND: J16.6 (VSS), J16.9 (DET_B), J16.11 (SHIELD); also elsewhere on the board

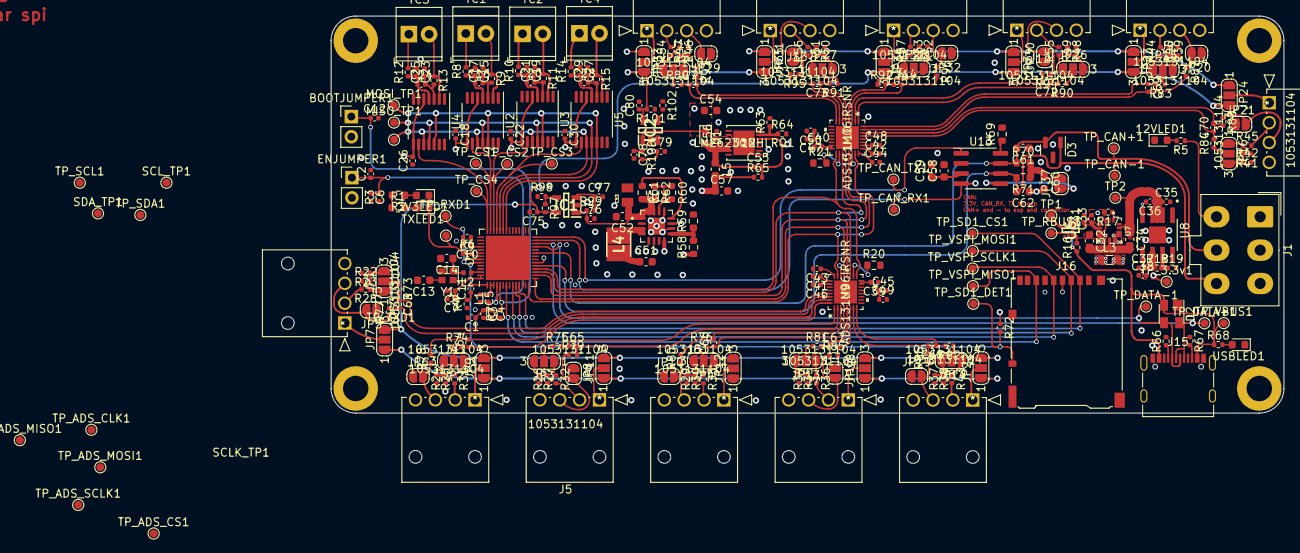
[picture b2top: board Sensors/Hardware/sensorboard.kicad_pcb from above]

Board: 4 copper layers, 120.0 x 50.0 mm, 306 parts (0 on the bottom side), 191 nets.

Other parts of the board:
C15, C17, C19, C21, C27, C29: 0.01uF; C_0402_1005Metric
C16, C18, C20, C22, C28, C30: 0.1uF; C_0402_1005Metric
C58: 100nF; C_0603_1608Metric
C59: 10uF; C_0603_1608Metric
C60: 0.1uF; C_0603_1608Metric
C61: 220pF; C_0603_1608Metric
C62: 220 pF; C_0603_1608Metric
D3: SM712_SOT23; SOT-23
JP37: TermJP; SolderJumper-2_P1.3mm_Open_RoundedPad1.0x1.5mm
R8, R9, R10, R11, R14, R15: 100; R_0402_1005Metric
R69: 0; R_0603_1608Metric
R70, R71: 60; R_0603_1608Metric
SCL_TP1: TestPoint; TestPoint_Pad_D1.0mm
SDA_TP1: TestPoint; TestPoint_Pad_D1.0mm
TC1, TC2, TC4: Thermocouple; TerminalBlock_TE_282834-2_1x02_P2.54mm_Horizontal
TP_SCL1: TestPoint; TestPoint_Pad_D1.0mm
TP_SDA1: TestPoint; TestPoint_Pad_D1.0mm
U2, U3, U5: MAX31856; TSSOP-14_4.4x5mm_P0.65mm
U13: SN65HVD230; SOIC-8_3.9x4.9mm_P1.27mm

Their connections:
+3V3: C18.2, C22.2, C30.2, C58.1, C59.1, U2.5 (AVDD), U2.8 (DVDD), U3.5 (AVDD), U3.8 (DVDD), U5.5 (AVDD), U5.8 (DVDD), U13.3 (VCC); also elsewhere on the board
/CAN+: C61.2, D3.2 (A2), R70.1, U13.7 (CANH); also elsewhere on the board
/CAN-: C62.2, D3.1 (A1), R71.2, U13.6 (CANL); also elsewhere on the board
/CAN-BUS/Vref: JP37.1 (A), U13.5 (Vref)
/CAN_RX: U13.4 (R); also elsewhere on the board
/CAN_TX: U13.1 (D); also elsewhere on the board
/CS0: U2.9 (~CS); also elsewhere on the board
/CS1: U3.9 (~CS); also elsewhere on the board
/CS2: U5.9 (~CS); also elsewhere on the board
/MISO: U2.11 (SDO), U3.11 (SDO), U5.11 (SDO); also elsewhere on the board
/MOSI: U2.12 (SDI), U3.12 (SDI), U5.12 (SDI); also elsewhere on the board
/SCL: SCL_TP1.1, TP_SCL1.1
/SCLK: U2.10 (SCK), U3.10 (SCK), U5.10 (SCK); also elsewhere on the board
/SDA: SDA_TP1.1, TP_SDA1.1
GND: C15.1, C17.2, C18.1, C19.1, C21.2, C22.1, C27.1, C29.2, C30.1, C58.2, C59.2, C60.2, C61.1, C62.1, D3.3 (common), R69.2, U2.1 (AGND), U2.14 (DGND), U3.1 (AGND), U3.14 (DGND), U5.1 (AGND), U5.14 (DGND), U13.2 (GND); also elsewhere on the board
unnamed: C60.1, JP37.2 (B), R70.2, R71.1
unnamed: R8.2, TC1.1 (+)
unnamed: R9.1, TC1.2 (-), U2.2 (BIAS)
unnamed: R10.2, TC2.1 (+)
unnamed: R11.1, TC2.2 (-), U3.2 (BIAS)
unnamed: R14.2, TC4.1 (+)
unnamed: R15.1, TC4.2 (-), U5.2 (BIAS)
unnamed: C15.2, C16.1, R8.1, U2.4 (T+)
unnamed: C16.2, C17.1, R9.2, U2.3 (T-)
unnamed: C19.2, C20.1, R10.1, U3.4 (T+)
unnamed: C20.2, C21.1, R11.2, U3.3 (T-)
unnamed: C27.2, C28.1, R14.1, U5.4 (T+)
unnamed: C28.2, C29.1, R15.2, U5.3 (T-)
unnamed: R69.1, U13.8 (Rs)
